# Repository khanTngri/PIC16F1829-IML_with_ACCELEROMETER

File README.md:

# PIC16F1829-IML_with_ACCELEROMETER
Licensed under CERN-OHL-S v2

A simple microcontroller board with RGB LED and accelerometer. Created with tutorial from Robert Feranec on YouTube as a learning material.
Links:
YouTube guide from Robert - https://www.youtube.com/watch?v=_x2fzKEjUGQ&list=PLXvLToQzgzdea0sQXmpY8k4tfiXpkYIwO
Eventually this PCB will be used for a Magic Wand (like in Harry Potter) project
Many thanks to Robert's guide.

## License

This project is licensed under the CERN Open Hardware Licence Version 2 – Strongly Reciprocal (CERN-OHL-S v2).

You may use, modify and manufacture this design, provided that any distributed modifications
are released under the same license.

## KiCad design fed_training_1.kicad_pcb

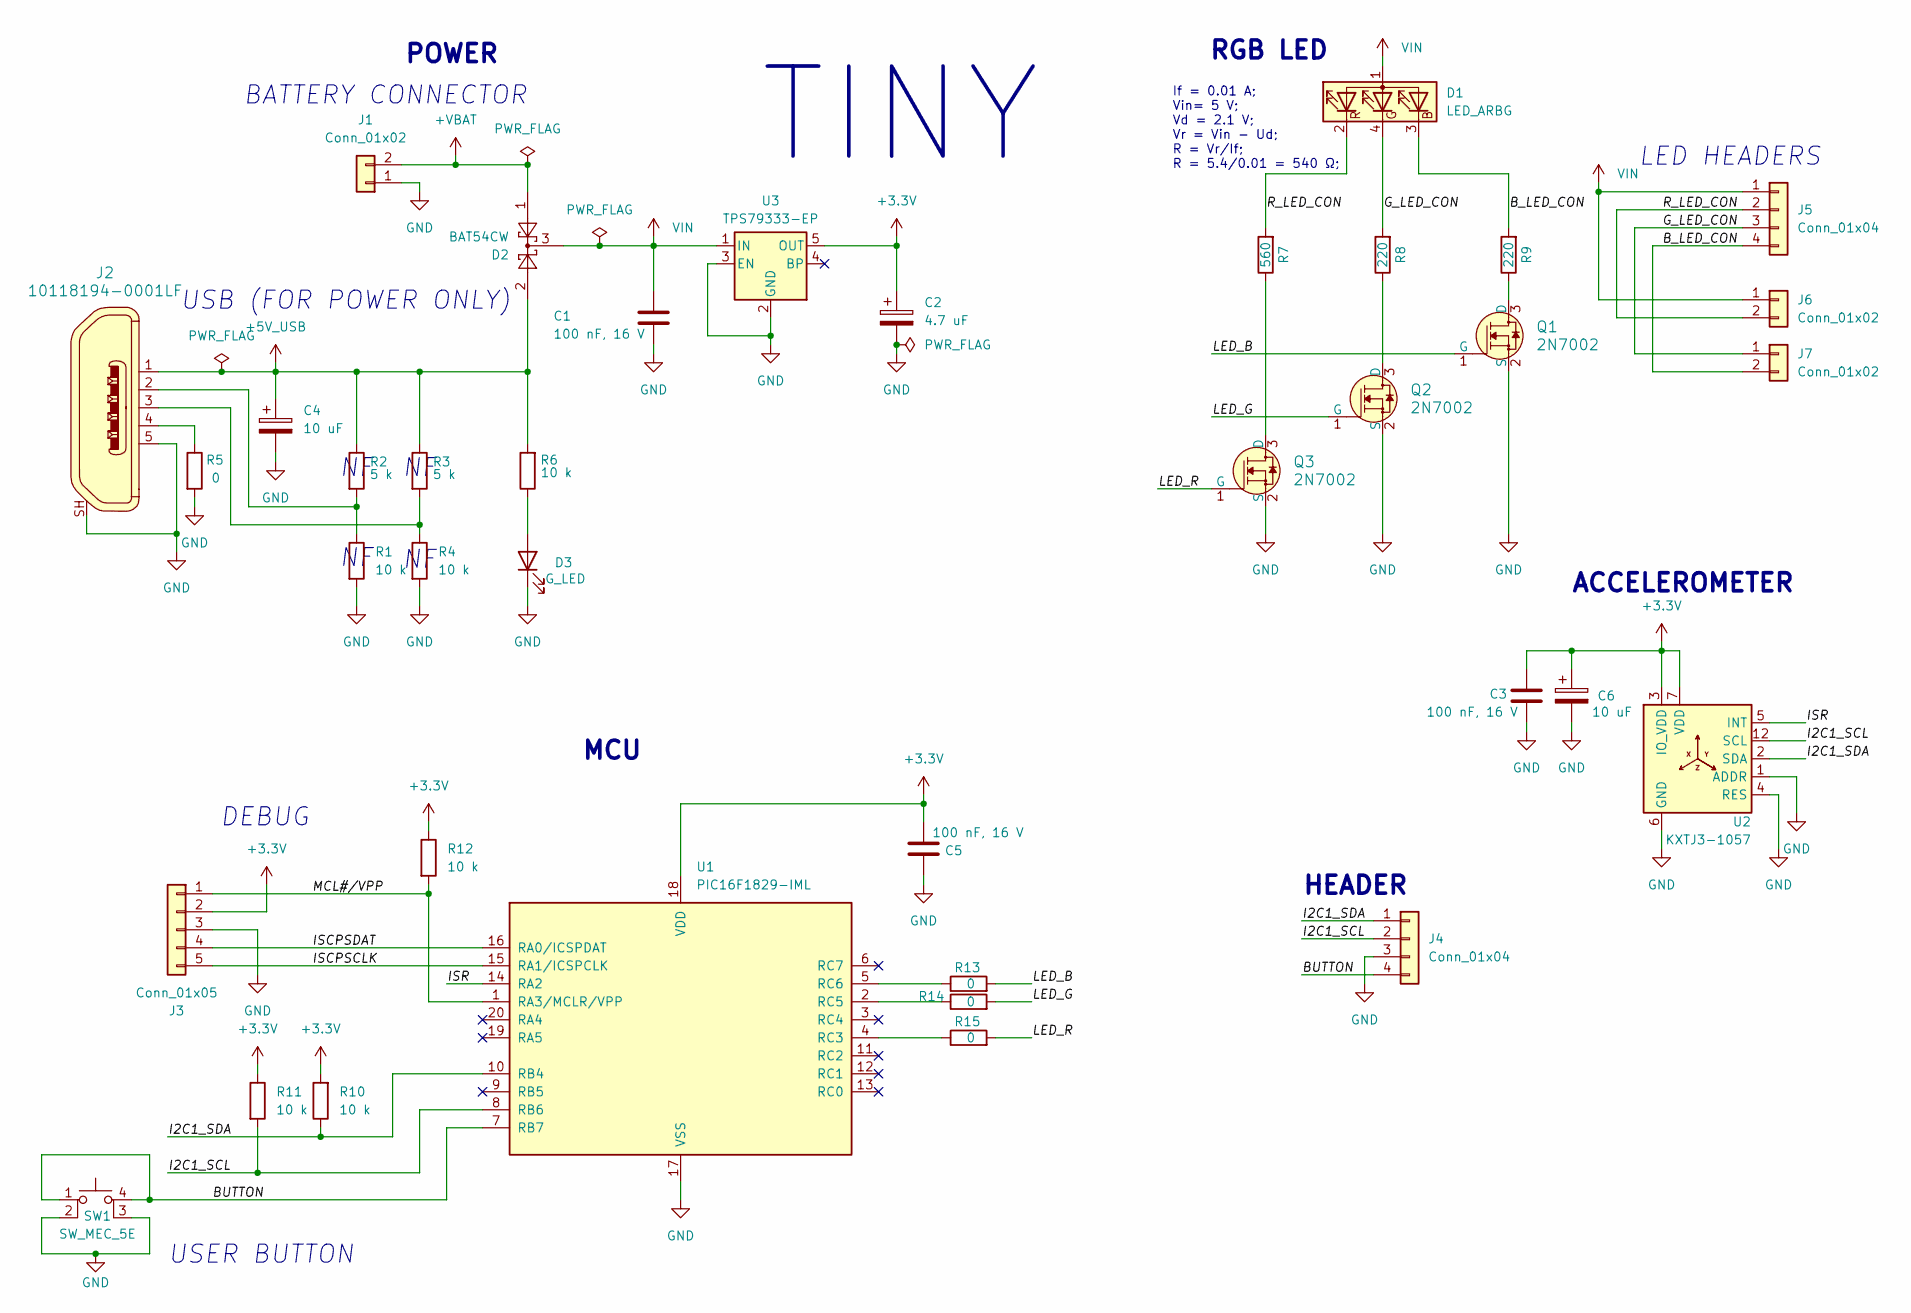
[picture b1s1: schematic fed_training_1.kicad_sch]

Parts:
C1, C3, C5: 100 nF, 16 V; C_0201_0603Metric_Pad0.64x0.40mm_HandSolder
C2: 4.7 uF; CP_EIA-3216-10_Kemet-I
C4, C6: 10 uF; CP_EIA-3216-10_Kemet-I
D1: LED_ARBG; LED_RGB_Wuerth-PLCC4_3.2x2.8mm_150141M173100
D2: BAT54CW; SOT-323_SC-70
D3: G_LED; LED_0805_2012Metric
J1, J6, J7: Conn_01x02; PinHeader_1x02_P1.27mm_Vertical
J2: 10118194-0001LF; USB_Micro_B_Female_10118194-0001LF; MPN 10118194-0001LF; Digi-Key_PN 609-4618-1-ND
J3: Conn_01x05; PinHeader_1x05_P1.00mm_Horizontal
J4, J5: Conn_01x04; PinHeader_1x04_P2.54mm_Vertical
Q1, Q2, Q3: 2N7002; SOT-23; MPN 2N7002; Digi-Key_PN 2N7002NCT-ND
R1, R4, R6, R10, R11, R12: 10 k; R_0603_1608Metric_Pad0.98x0.95mm_HandSolder
R2, R3: 5 k; R_0603_1608Metric_Pad0.98x0.95mm_HandSolder
R5, R13, R14, R15: 0; R_0603_1608Metric_Pad0.98x0.95mm_HandSolder
R7: 560; R_0603_1608Metric_Pad0.98x0.95mm_HandSolder
R8, R9: 220; R_0603_1608Metric_Pad0.98x0.95mm_HandSolder
SW1: SW_MEC_5E; SW_TH_Tactile_Omron_B3F-102x
U1: PIC16F1829-IML; SSOP-20_5.3x7.2mm_P0.65mm
U2: KXTJ3-1057; Kionix_LGA-12_2x2mm_P0.5mm_LayoutBorder2x4y
U3: TPS79333-EP; SOT-23-5

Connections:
+3.3V: C2.1, C3.2, C5.1, C6.1, J3.2, R10.2, R11.1, R12.1, U1.18 (VDD), U2.3 (IO_VDD), U2.7 (VDD), U2.10 (VDD), U2.11 (IO_VDD), U3.5 (OUT)
+5V_USB: C4.1, D2.2, J2.1, R2.1, R3.1, R6.2
+VBAT: D2.1, J1.2
/BUTTON: J4.4, SW1.1, SW1.4 (A), U1.7 (RB7)
/B_LED_CON: D1.3 (BK), J5.4, J7.2, R9.2
/G_LED_CON: D1.4 (GK), J5.3, J7.1, R8.2
/I2C1_SCL: J4.2, R11.2, U1.8 (RB6), U2.12 (SCL)
/I2C1_SDA: J4.1, R10.1, U1.10 (RB4), U2.2 (SDA)
/ISCPSCLK: J3.5, U1.15 (RA1/ICSPCLK)
/ISCPSDAT: J3.4, U1.16 (RA0/ICSPDAT)
/ISR: U1.14 (RA2), U2.5 (INT)
/LED_B: Q1.1 (G), R13.2
/LED_G: Q2.1 (G), R14.2
/LED_R: Q3.1 (G), R15.2
/MCL#/VPP: J3.1, R12.2, U1.1 (RA3/MCLR/VPP)
/R_LED_CON: D1.2 (RK), J5.2, J6.2, R7.2
GND: C1.1, C2.2, C3.1, C4.2, C5.2, C6.2, D3.1 (K), J1.1, J2.5, J2.SH, J3.3, J4.3, Q1.2 (S), Q2.2 (S), Q3.2 (S), R1.2, R4.2, R5.2, SW1.2, SW1.3 (K), U1.17 (VSS), U2.1 (ADDR), U2.4 (RES), U2.6 (GND), U2.8 (GND), U2.9 (GND), U3.2 (GND), U3.3 (EN)
unnamed: D3.2 (A), R6.1
unnamed: J2.2, R1.1, R2.2
unnamed: J2.3, R3.2, R4.1
unnamed: J2.4, R5.1
unnamed: Q1.3 (D), R9.1
unnamed: Q2.3 (D), R8.1
unnamed: Q3.3 (D), R7.1
unnamed: R15.1, U1.4 (RC3)
unnamed: R14.1, U1.2 (RC5)
unnamed: R13.1, U1.5 (RC6)
VIN: C1.2, D1.1 (A), D2.3, J5.1, J6.1, U3.1 (IN)

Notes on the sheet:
HEADER
BATTERY CONNECTOR
If = 0.01 A; Vin= 5 V; Vd = 2.1 V; Vr = Vin - Ud; R = Vr/If; R = 5.4/0.01 = 540 Ω;
RGB LED
USER BUTTON
ACCELEROMETER
LED HEADERS
TINY
DEBUG
USB (FOR POWER ONLY)
MCU
POWER

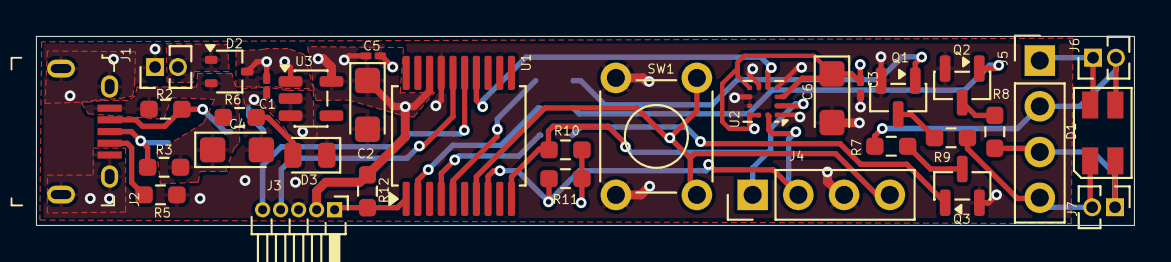
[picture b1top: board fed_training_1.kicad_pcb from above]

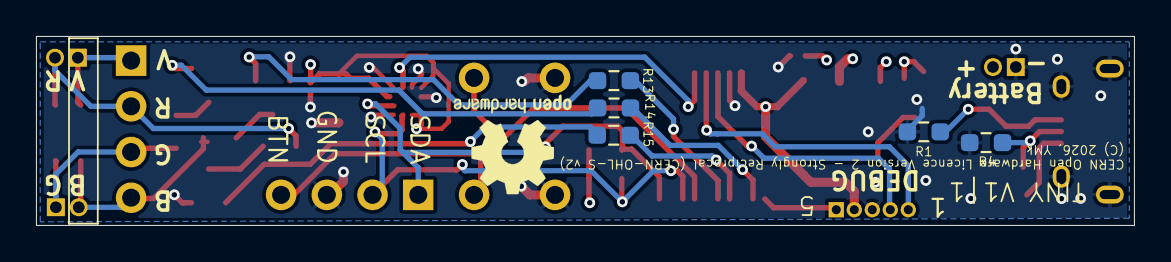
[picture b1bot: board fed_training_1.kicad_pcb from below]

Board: 4 copper layers, 61.0 x 10.5 mm, 38 parts (5 on the bottom side), 28 nets.

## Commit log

2026-01-30 Update LICENSE
2026-01-30 Initial KiCad project upload
2026-01-30 Initial KiCad project (schematic and PCB)

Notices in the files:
fed_training_1.kicad_pcb:
(C) 2026, YMk
